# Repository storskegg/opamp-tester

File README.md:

# opamp-tester

A simple tester for OpAmps. This is a gratuitous copy of the schematic shown in
@IMSAIGuy's videos; see link below.

The reason why I did this build is that I wanted to add support for testing single
opamps in addition to dual and quad. Additionally, I chose to space things out a bit
so that I can solder ZIF sockets.

For the life of me I could not find ZIF sockets under 14 pins, so...ja, all three
sockets are 14-pin.

## References

- IMSAIGuy: https://www.pcbway.com/project/shareproject/Dual_and_Quad_OpAmp_SImple_Tester_f0fc4495.html
- ZIF socket: https://www.amazon.com/PATIKIL-Universal-Microcontroller-Breadboard-Program/dp/B0BWN5K142?th=1

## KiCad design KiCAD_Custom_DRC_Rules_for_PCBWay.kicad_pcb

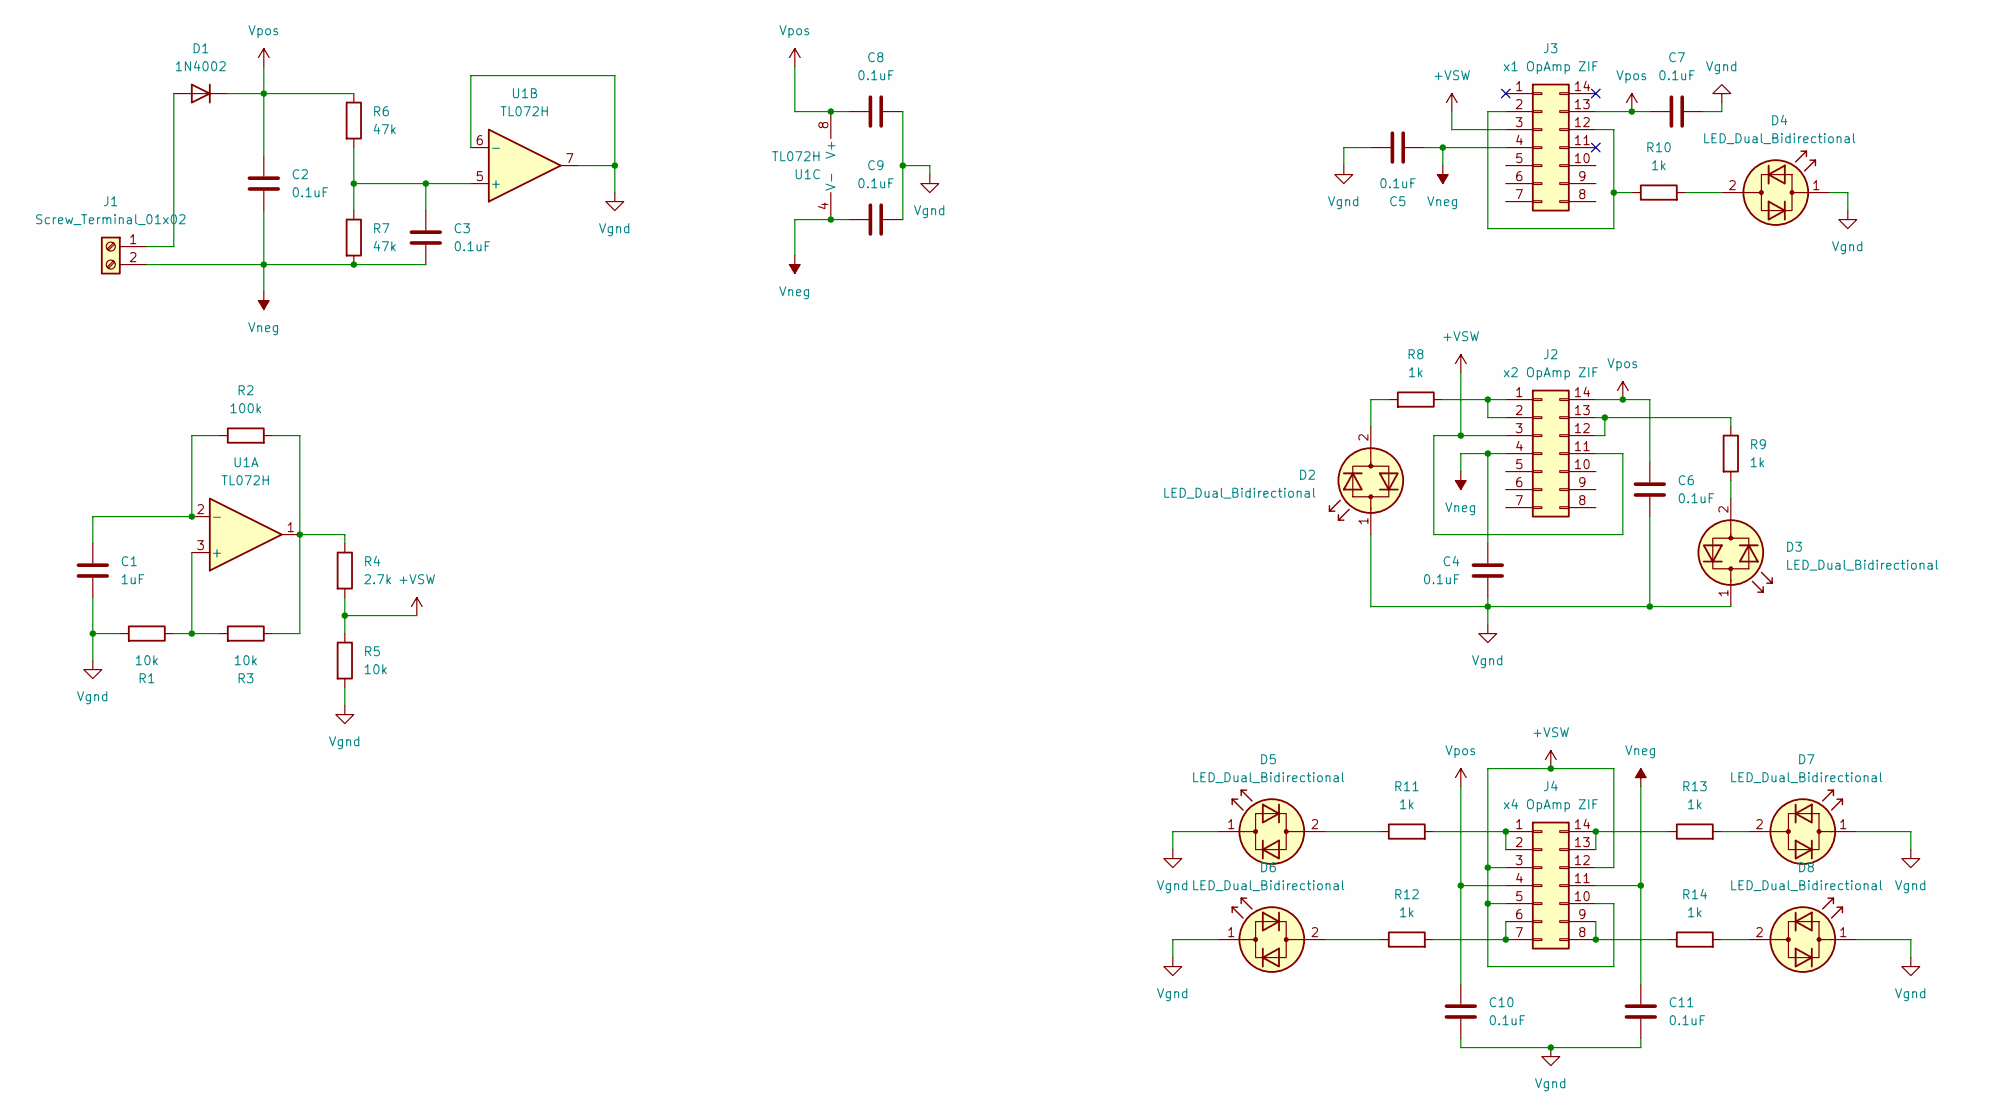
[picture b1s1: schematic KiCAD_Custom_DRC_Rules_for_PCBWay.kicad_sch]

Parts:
C1: 1uF; C_0805_2012Metric
C2, C3, C4, C5, C6, C7, C8, C9, C10, C11: 0.1uF; C_0805_2012Metric
D1: 1N4002; D_DO-41_SOD81_P10.16mm_Horizontal
D2, D3, D4, D5, D6, D7, D8: LED_Dual_Bidirectional; LED_0805_2012Metric
J1: Screw_Terminal_01x02; TerminalBlock_Altech_AK300-2_P5.00mm
J2: x2 OpAmp ZIF; CERDIP-14_W7.62mm_SideBrazed_LongPads_Socket
J3: x1 OpAmp ZIF; CERDIP-14_W7.62mm_SideBrazed_LongPads_Socket
J4: x4 OpAmp ZIF; CERDIP-14_W7.62mm_SideBrazed_LongPads_Socket
R1, R3, R5: 10k; R_0805_2012Metric
R2: 100k; R_0805_2012Metric
R4: 2.7k; R_0805_2012Metric
R6, R7: 47k; R_0805_2012Metric
R8, R9, R10, R11, R12, R13, R14: 1k; R_0805_2012Metric
U1: TL072H; SOIC-8_3.9x4.9mm_P1.27mm

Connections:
+VSW: J2.3, J2.11, J3.3, J4.3, J4.5, J4.10, J4.12, R4.2, R5.1
unnamed: D1.2 (A), J1.1
unnamed: D2.2 (AK), R8.2
unnamed: D3.2 (AK), R9.2
unnamed: D4.2 (AK), R10.2
unnamed: D5.2 (AK), R11.1
unnamed: D6.2 (AK), R12.1
unnamed: D7.2 (AK), R13.2
unnamed: D8.2 (AK), R14.2
unnamed: J2.1, J2.2, R8.1
unnamed: J2.12, J2.13, R9.1
unnamed: J3.2, J3.12, R10.1
unnamed: J4.1, J4.2, R11.2
unnamed: J4.6, J4.7, R12.2
unnamed: J4.8, J4.9, R14.1
unnamed: J4.13, J4.14, R13.1
unnamed: R2.2, R3.1, R4.1, U1.1
unnamed: R1.1, R3.2, U1.3 (+)
unnamed: C1.1, R2.1, U1.2 (-)
unnamed: C3.1, R6.2, R7.1, U1.5 (+)
Vgnd: C1.2, C4.2, C5.2, C6.2, C7.2, C8.1, C9.2, C10.2, C11.2, D2.1 (KA), D3.1 (KA), D4.1 (KA), D5.1 (KA), D6.1 (KA), D7.1 (KA), D8.1 (KA), R1.2, R5.2, U1.6 (-), U1.7
Vneg: C2.2, C3.2, C4.1, C5.1, C9.1, C11.1, J1.2, J2.4, J3.4, J4.11, R7.2, U1.4 (V-)
Vpos: C2.1, C6.1, C7.1, C8.2, C10.1, D1.1 (K), J2.14, J3.13, J4.4, R6.1, U1.8 (V+)

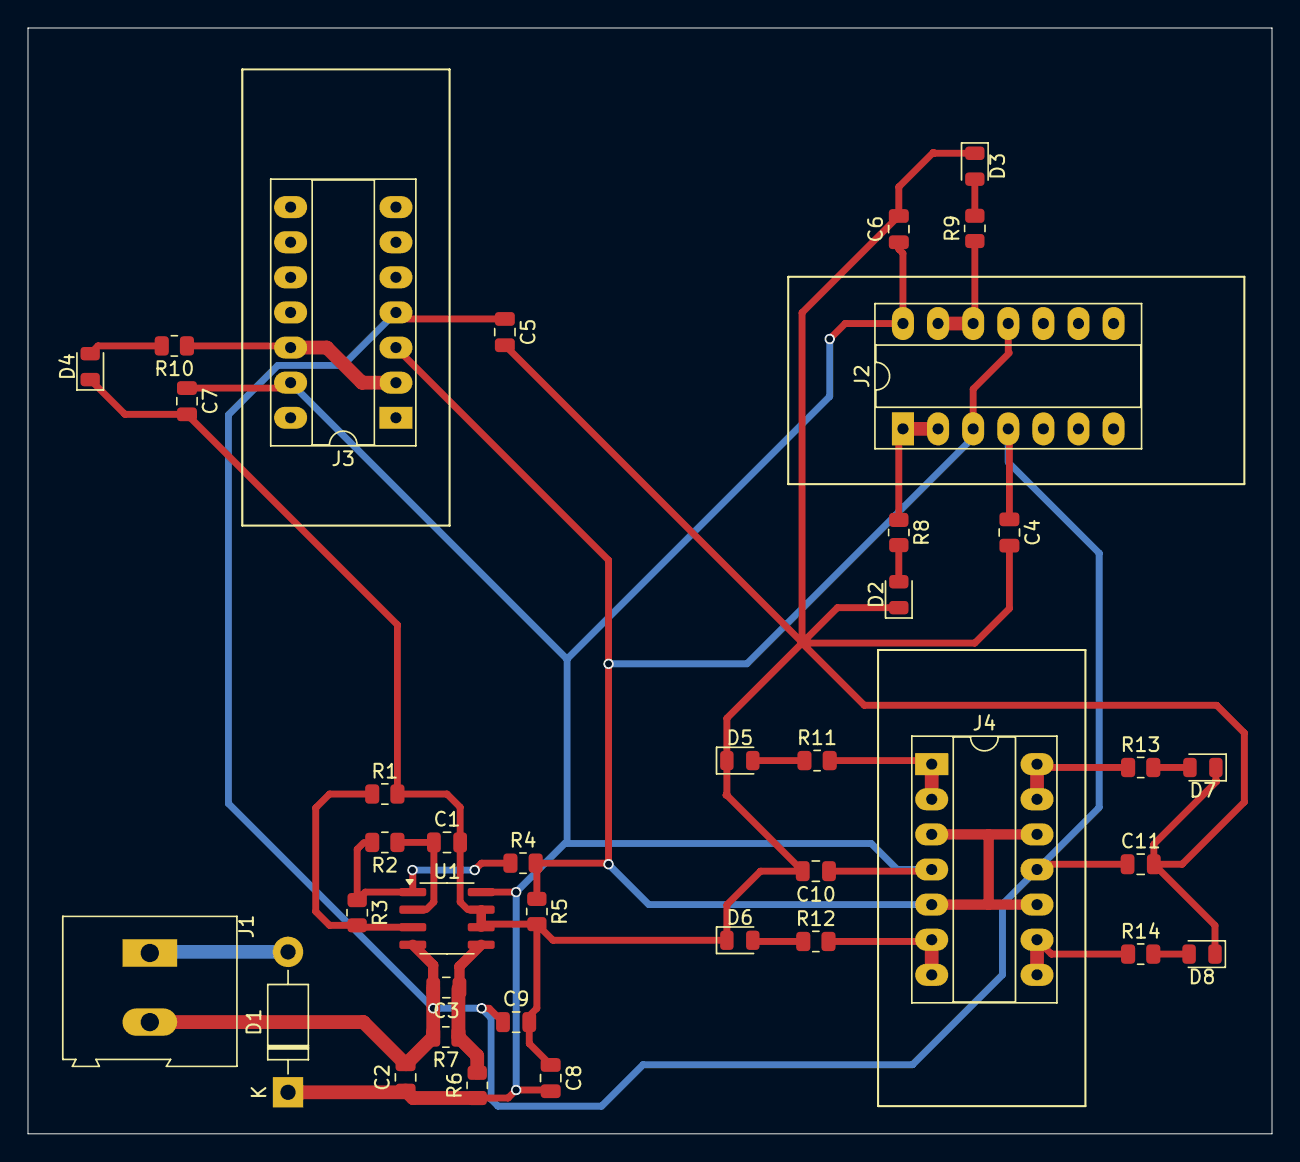
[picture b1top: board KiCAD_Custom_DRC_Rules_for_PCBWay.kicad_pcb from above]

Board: 2 copper layers, 90.0 x 80.0 mm, 38 parts (0 on the bottom side), 23 nets.

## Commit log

2024-11-04 update the readme
2024-11-04 add the new files
2024-11-04 [at]user imsaiguy
    imsai...if you get pinged, please excuse my super-amateur skillz.
2024-11-04 moving some traces around
2024-11-04 clean up the schematic a bit
2024-11-04 generate gerbers
2024-11-04 cleanup, datasheet updates, add BOM
2024-11-04 add lock files to gitignore
